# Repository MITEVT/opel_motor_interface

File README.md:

# opel_motor_interface
Firmware for MIT EVT's Opel GT Motor Interface Module

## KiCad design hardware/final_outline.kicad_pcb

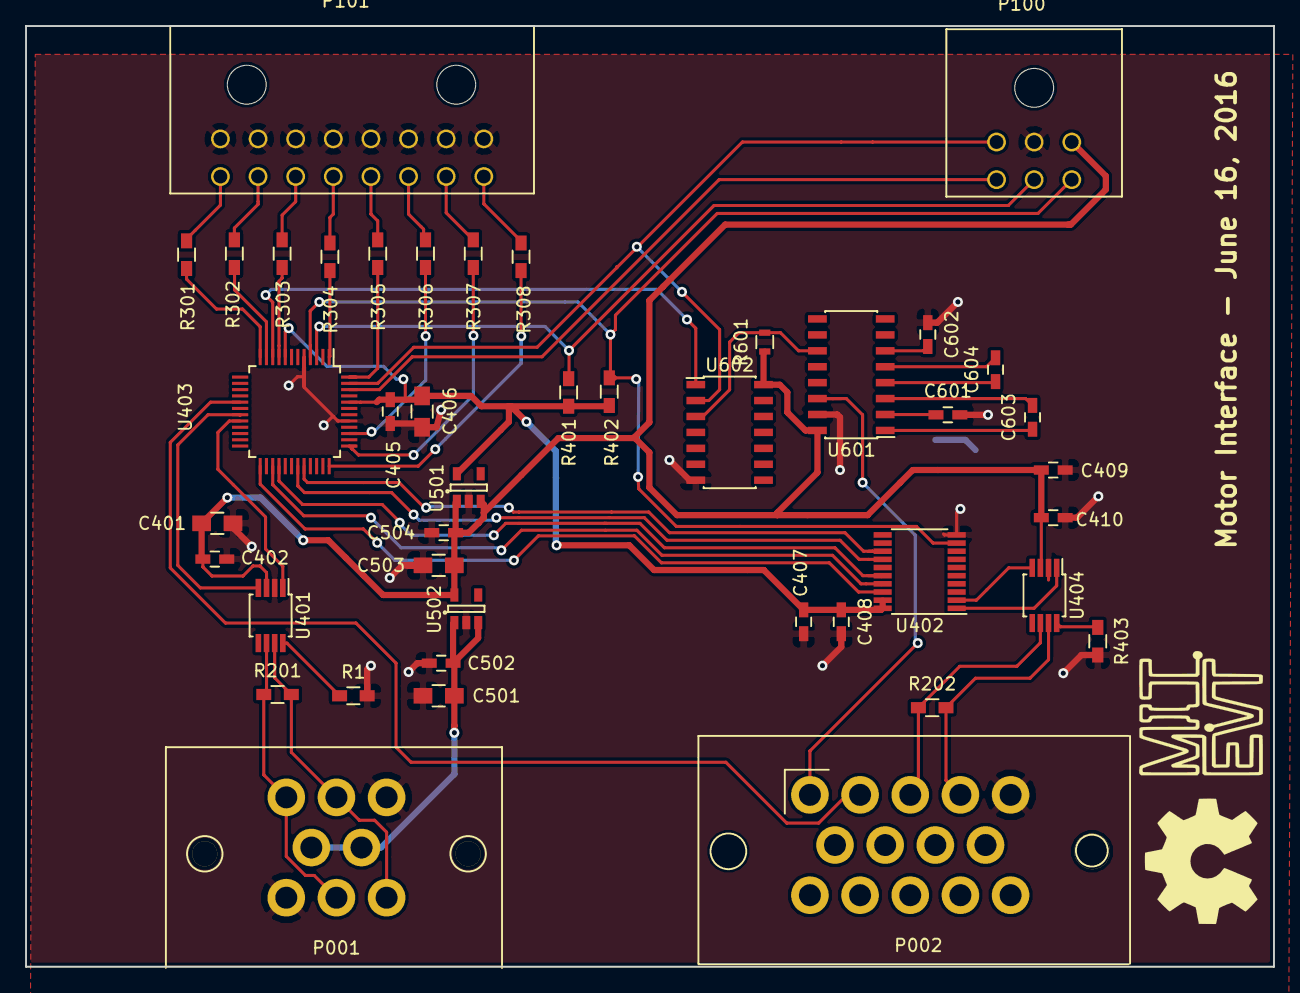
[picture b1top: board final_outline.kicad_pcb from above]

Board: 2 copper layers, 99.5 x 75.0 mm, 43 parts (0 on the bottom side), 49 nets.

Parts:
C401, C406: 10uF; C_0805_HandSoldering
C402, C405: 0.1uF; C_0603_HandSoldering
C407, C409, C601, C602, C603, C604: 1μF; C_0603_HandSoldering
C408, C410: .1μF; C_0603_HandSoldering
C501, C503: 10μ; C_0805_HandSoldering
C502, C504: .1μ; C_0603_HandSoldering
P001: CANCONNECTOR; 776280-1
P002: CONN_01X14; 776267-1
P100: ISP; Connector_Microfit3_Header_02x03_Angled_43045-060x
P101: DEBUG_LED; Connector_Microfit3_Header_02x08_Angled_43045-160x
R1: 20k; R_0603_HandSoldering
R201, R202: 120; R_0603_HandSoldering
R301, R302, R303, R304, R305, R306, R307, R308: 100; R_0603_HandSoldering
R401, R402: 10k; R_0603_HandSoldering
R403: 20K; R_0603_HandSoldering
R601: 20K; R_0603
U401, U404: MCP2551-I/SN; MSOP-8_3x3mm_Pitch0.65mm
U402: MCP2515_TSSOP; TSSOP-20_4.4x6.5mm_Pitch0.65mm
U403: LPC11C14; LQFP-48_7x7mm_Pitch0.5mm
U501: MCP1755-33; SOT-23-5
U502: MCP1755-5; SOT-23-5
U601: MAX232; SOIC-16_3.9x9.9mm_Pitch1.27mm
U602: SN74HCT125; SOIC-14_3.9x8.7mm_Pitch1.27mm

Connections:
+3V3: C405.1, C406.1, C407.1, C408.1, R401.1, R402.1, U402.19, U402.20, U403.8, U403.44, U501.5
+5V: C401.1, C402.1, C409.1, C410.1, C503.1, C504.1, P100.3, R601.1, U401.3, U404.3, U501.1, U501.3, U502.5, U601.16, U602.14
+12V: C501.2, C502.1, P001.4, P001.5, U502.1, U502.3
/BACK_PANEL/CANH: P001.2, P001.8, R201.2, U401.7
/BACK_PANEL/CANH2: P002.4, R202.2, U404.7
/BACK_PANEL/CANL: P001.1, P001.7, R201.1, U401.6
/BACK_PANEL/CANL2: P002.3, R202.1, U404.6
/BACK_PANEL/DC/DC_CTRL: P002.2, U403.17
/BACK_PANEL/RS232_MSG: P002.1, U601.14
/FRONT_PANEL/LED0: R301.1, U403.12
/FRONT_PANEL/LED1: R302.2, U403.11
/FRONT_PANEL/LED2: R303.2, U403.9
/FRONT_PANEL/LED3: R304.1, U403.1
/FRONT_PANEL/LED4: R305.2, U403.48
/FRONT_PANEL/LED5: R306.1, U403.39
/FRONT_PANEL/LED6: R307.2, U403.37
/FRONT_PANEL/LED7: R308.1, U403.36
/FRONT_PANEL/MCU_PROG_N: P100.6, R402.2, U402.9, U403.4
/FRONT_PANEL/MCU_RESET_N: P100.5, R401.2, U403.3
/FRONT_PANEL/RXD: P100.4, U403.46
/FRONT_PANEL/TXD: P100.1, U403.47, U602.2
/Micro_Controller/CAN_RXD: U401.4, U403.19
/Micro_Controller/CAN_TXD: U401.1, U403.20
/Micro_Controller/PIO0_11: U402.13, U403.32
/Micro_Controller/RS232_CTRL: U403.10, U602.1
GND: C401.2, C402.2, C405.2, C406.2, C407.2, C408.2, C409.2, C410.2, C501.1, C502.2, C503.2, C504.2, C601.2, C602.1, P001.3, P001.6, P002.5, P100.2, P101.1, P101.2, P101.3, P101.4, P101.5, P101.6, P101.7, P101.8, R1.2, R403.2, U401.2, U402.10, U403.5, U403.41, U404.2, U501.2, U502.2, U601.15, U602.7
unnamed: C601.1, U601.2
unnamed: C602.2, U601.6
unnamed: C603.1, U601.1
unnamed: C603.2, U601.3
unnamed: C604.1, U601.4
unnamed: C604.2, U601.5
unnamed: P101.9, R301.2
unnamed: P101.10, R302.1
unnamed: P101.11, R303.1
unnamed: P101.12, R304.2
unnamed: P101.13, R305.1
unnamed: P101.14, R306.2
unnamed: P101.15, R307.1
unnamed: P101.16, R308.2
unnamed: R1.1, U401.8
unnamed: R403.1, U404.8
unnamed: R601.2, U601.11, U602.3
unnamed: U402.1, U404.1
unnamed: U402.2, U404.4
unnamed: U402.14, U403.31
unnamed: U402.16, U403.28
unnamed: U402.17, U403.27
unnamed: U402.18, U403.25

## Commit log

2015-11-07 Updated .gitignore
2016-04-23 Initial Firmware commit
2016-04-23 Initial work with AZD motor controller
2016-04-23 Started DMOC header
2016-04-24 Progess of decoding shit
2016-04-24 Decodes stuff
2016-04-30 Lots of stuff, Moves on from CAN Errors, Has more states
2016-05-01 Motor Spins
2016-05-07 Drive motor at different speeds, ramps to speeds
2016-06-02 Sends initial RS232 message
2016-06-03 began code cleanup and commenting
2016-06-03 Added some comments, fixed code warnings
2016-06-03 Final version before adding in DC/DC converter
2016-06-03 Added alternate motor interface and python serial data display
2016-06-05 Some updates to the display, including formatting
2016-06-05 Changes to alternative firmware to fix formatting with GUI
2016-06-11 Switched CAN buses, added output message
2016-06-16 Initial PCB
2016-06-16 Final version of board
2016-06-20 Added auto-startup sequence
2016-06-22 Gave full control to the rest of the vehicle
2016-07-01 Fixed some messages
2016-07-05 Reverse works if power cycled
2016-07-07 Fixed state numbering, fixed forward/reverse switching
